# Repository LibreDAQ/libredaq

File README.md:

# LibreDAQ official repository

LibreDAQ is a versatile, modular and hackable Data Acquisition (DAQ) platform. 
This repository includes the sources for: 
* Circuit schematics
* C++ SDK
* C++ examples
* Firmware
* ROS node
* LibreDAQStudio

# Cite as: 

* Blanco-Claraco, J. L., López-Martínez, J., Torres-Moreno, J. L., & Giménez-Fernández, A. (2015). **A Low-Cost Modular Platform for Heterogeneous Data Acquisition with Accurate Interchannel Synchronization**. *Sensors*, 15(10), 27374-27392 ([PDF](https://www.mdpi.com/1424-8220/15/10/27374/pdf)).
* BibTex:
```
@article{blanco2015low,
  title={A Low-Cost Modular Platform for Heterogeneous Data Acquisition with Accurate Interchannel Synchronization},
  author={Blanco-Claraco, Jos{\'e} Luis and L{\'o}pez-Mart{\'\i}nez, Javier and Torres-Moreno, Jos{\'e} Luis and Gim{\'e}nez-Fern{\'a}ndez, Antonio},
  journal={Sensors},
  volume={15},
  number={10},
  pages={27374--27392},
  year={2015}
}
```

# CircuitHub

* [LibreDAQ Base board](https://circuithub.com/projects/LibreDAQ/ldaq-base-v11)

# Videos:

[YouTube playlist](https://www.youtube.com/playlist?list=PLOJ3GF0x2_eULIKMOQqdDnZAjOUo_N2IJ)

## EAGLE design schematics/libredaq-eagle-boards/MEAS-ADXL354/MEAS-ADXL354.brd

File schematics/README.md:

All LibreDAQ schematics are published under the following License:

[Attribution-NonCommercial-ShareAlike 4.0 International](https://creativecommons.org/licenses/by-nc-sa/4.0/)

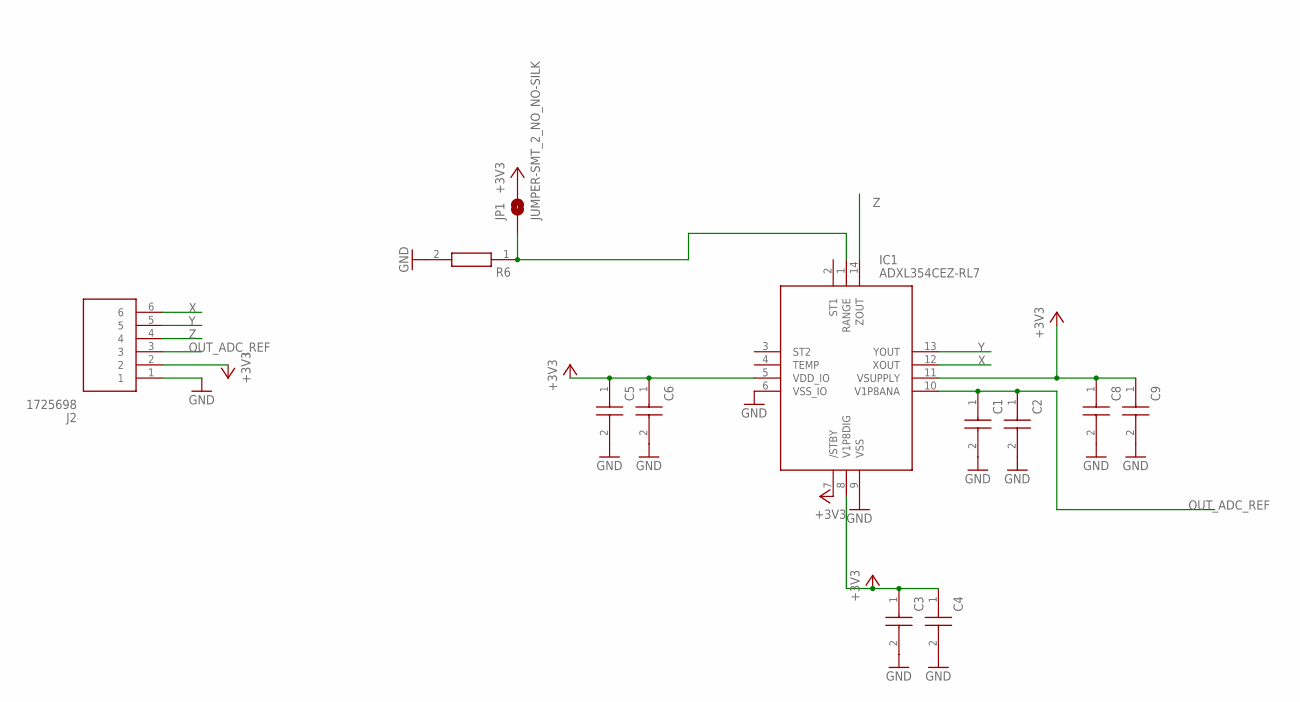
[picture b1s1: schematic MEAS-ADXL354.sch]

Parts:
C1, C3, C5, C8: 1.0uF; CAPC1005X55N
C2, C4, C6, C9: 0.1uF; CAPC1005X55N
IC1: ADXL354CEZ-RL7; PLCC127P602X560X205-14N
J2: 1725698
JP1: JUMPER-SMT_2_NO_NO-SILK; SMT-JUMPER_2_NO_NO-SILK
R6: SFR03EZPF6801; RESC1608X55N

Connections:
+3V3: C3.1, C4.1, C5.1, C6.1, C8.1, C9.1, IC1.5 (VDD_IO), IC1.7 (/STBY), IC1.8 (V1P8DIG), IC1.11 (VSUPPLY), J2.2, JP1.2
GND: C1.2, C2.2, C3.2, C4.2, C5.2, C6.2, C8.2, C9.2, IC1.6 (VSS_IO), IC1.9 (VSS), J2.1, R6.2
unnamed: IC1.1 (RANGE), JP1.1, R6.1
OUT_ADC_REF: C1.1, C2.1, IC1.10 (V1P8ANA), J2.3
X: IC1.12 (XOUT), J2.6
Y: IC1.13 (YOUT), J2.5
Z: IC1.14 (ZOUT), J2.4

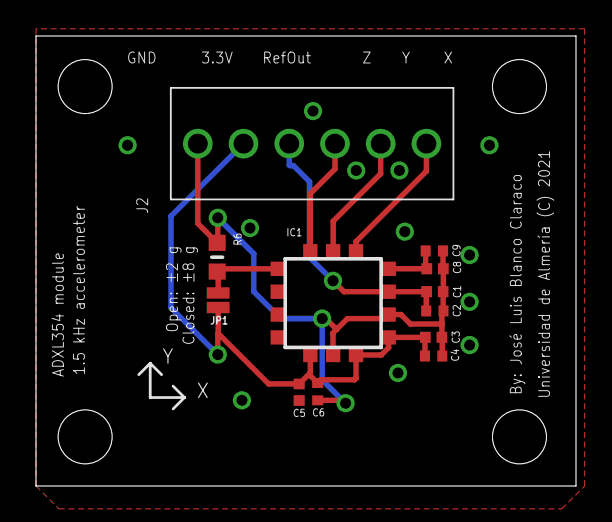
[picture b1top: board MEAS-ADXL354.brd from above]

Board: 2 copper layers, 30.0 x 25.0 mm, 12 parts (0 on the bottom side), 7 nets.

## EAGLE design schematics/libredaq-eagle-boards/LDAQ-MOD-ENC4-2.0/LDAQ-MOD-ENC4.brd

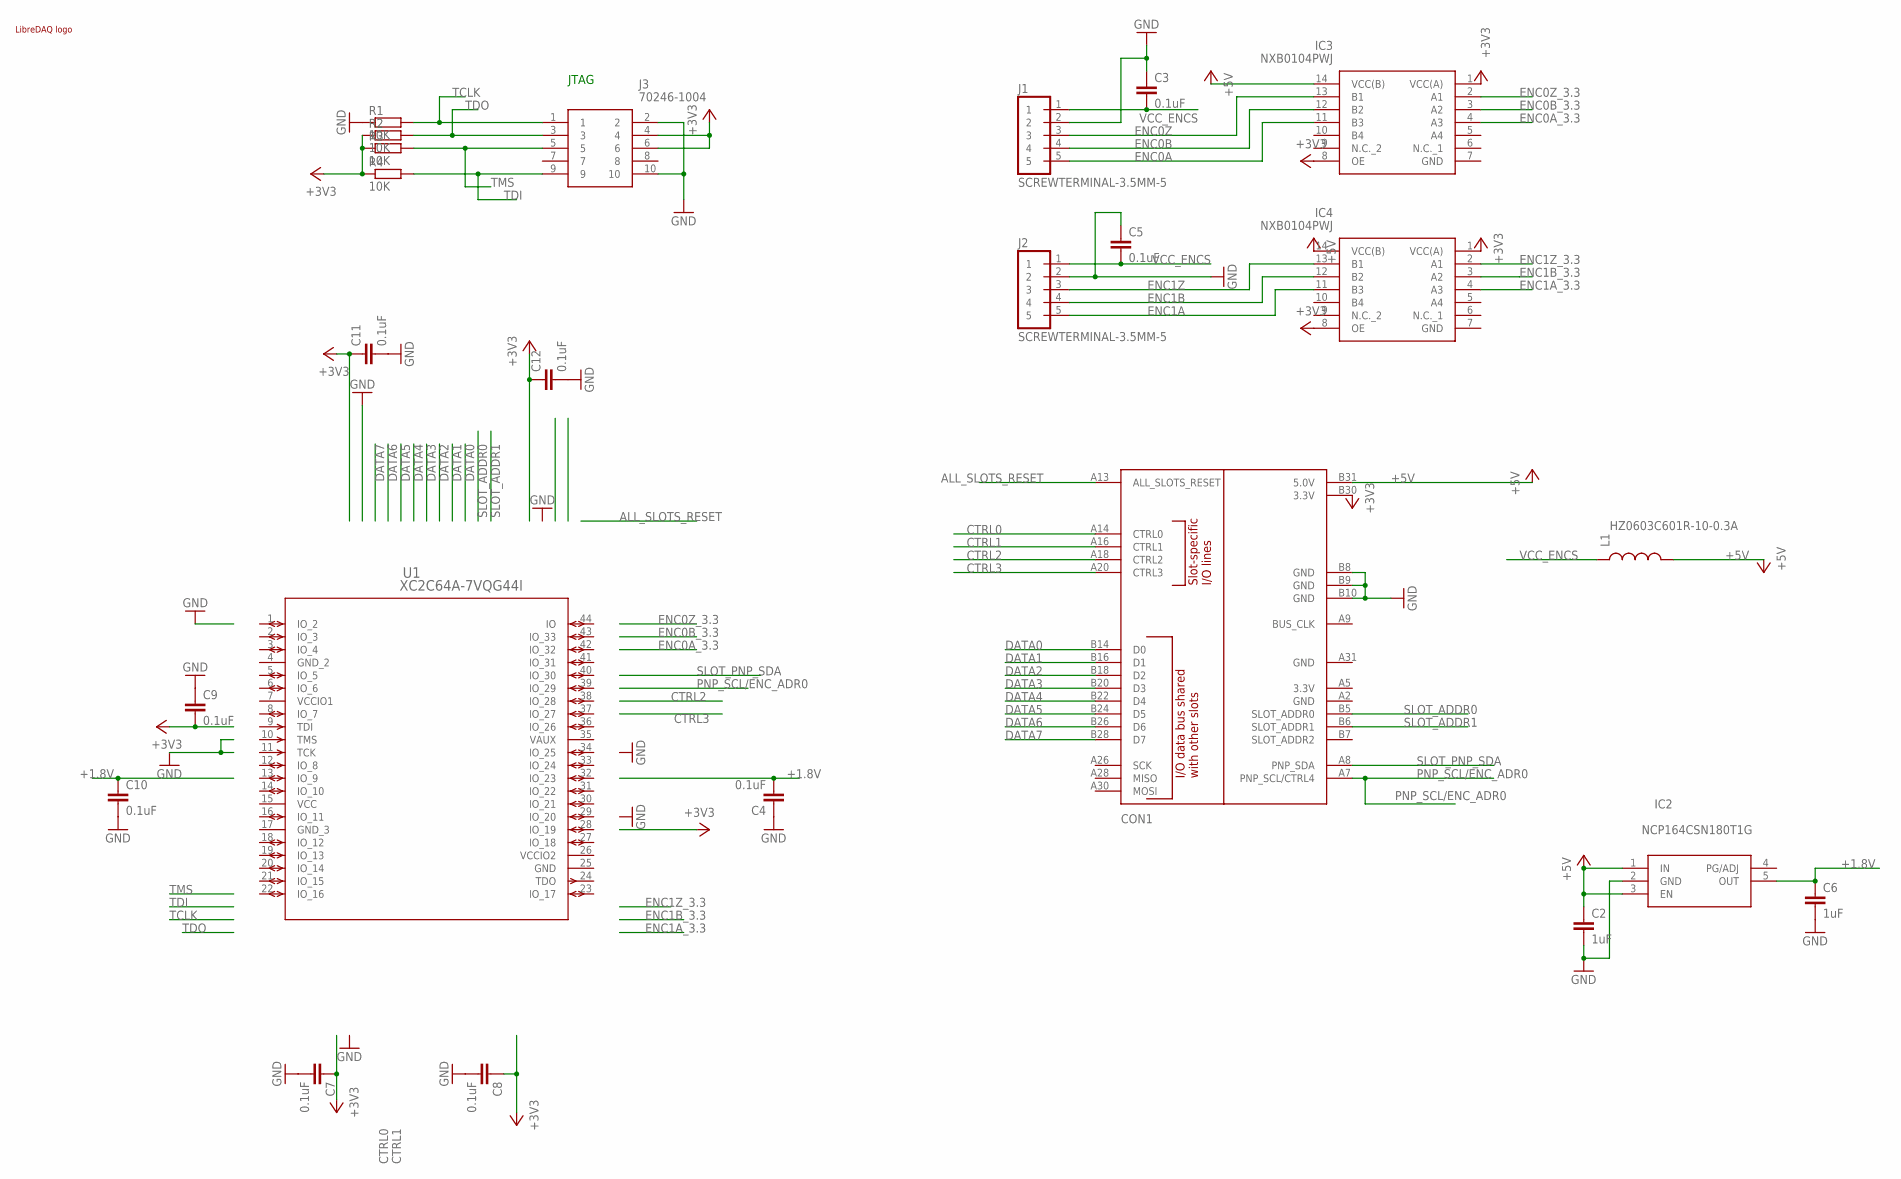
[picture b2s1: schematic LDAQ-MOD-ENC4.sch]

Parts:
C2, C6: 1uF; C0603
C3, C4, C5, C7, C8, C9, C10, C11, C12: 0.1uF; 0603-CAP
CON1: BOARD; PCI-E_64_EDGE_70X60_PADS-ONLY
IC2: NCP164CSN180T1G; SOT95P275X110-5N
IC3, IC4: NXB0104PWJ; SOP65P640X110-14N
J1, J2: SCREWTERMINAL-3.5MM-5
J3: 70246-1004; SHDR10W64P254_2X5_2032X889X927
L1: HZ0603C601R-10-0.3A; 0603
LOGO1: LIBREDAQ_LOGO_MINILOGO_GENERIC; LIBREDAQ_LOGO
R1, R2, R3, R4: 10K; R0603
U1: XC2C64A-7VQG44I; 44-VQFP_XIL

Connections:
+1.8V: C4.2, C6.1, C10.1, IC2.5 (OUT)
+3V3: C7.1, C8.1, C9.2, C11.1, C12.1, CON1.B30 (3.3V), IC3.1 (VCC(A)), IC3.8 (OE), IC4.1 (VCC(A)), IC4.8 (OE), J3.4, J3.6, R2.1, R3.1, R4.1
+5V: C2.1, CON1.B31 (5.0V), IC2.1 (IN), IC2.3 (EN), IC3.14 (VCC(B)), IC4.14 (VCC(B)), L1.2
ALL_SLOTS_RESET: CON1.A13 (ALL_SLOTS_RESET)
CTRL0: CON1.A14 (CTRL0)
CTRL1: CON1.A16 (CTRL1)
CTRL2: CON1.A18 (CTRL2)
CTRL3: CON1.A20 (CTRL3)
DATA0: CON1.B14 (D0)
DATA1: CON1.B16 (D1)
DATA2: CON1.B18 (D2)
DATA3: CON1.B20 (D3)
DATA4: CON1.B22 (D4)
DATA5: CON1.B24 (D5)
DATA6: CON1.B26 (D6)
DATA7: CON1.B28 (D7)
ENC0A: IC3.11 (B3), J1.5
ENC0A_3.3: IC3.4 (A3)
ENC0B: IC3.12 (B2), J1.4
ENC0B_3.3: IC3.3 (A2)
ENC0Z: IC3.13 (B1), J1.3
ENC0Z_3.3: IC3.2 (A1)
ENC1A: IC4.11 (B3), J2.5
ENC1A_3.3: IC4.4 (A3)
ENC1B: IC4.12 (B2), J2.4
ENC1B_3.3: IC4.3 (A2)
ENC1Z: IC4.13 (B1), J2.3
ENC1Z_3.3: IC4.2 (A1)
GND: C2.2, C3.1, C4.1, C5.1, C6.2, C7.2, C8.2, C9.1, C10.2, C11.2, C12.2, CON1.B8 (GND), CON1.B9 (GND), CON1.B10 (GND), IC2.2 (GND), J1.2, J2.2, J3.2, J3.10, R1.1, U1.25 (GND)
GND_2: U1.4 (GND_2)
GND_3: U1.17 (GND_3)
PNP_SCL/ENC_ADR0: CON1.A7 (PNP_SCL/CTRL4)
SLOT_ADDR0: CON1.B5 (SLOT_ADDR0)
SLOT_ADDR1: CON1.B6 (SLOT_ADDR1)
SLOT_PNP_SDA: CON1.A8 (PNP_SDA)
TCLK: J3.1, R1.2
TDI: J3.9, R4.2
TDO: J3.3, R2.2
TMS: J3.5, R3.2
VAUX: U1.35 (VAUX)
VCC: U1.15 (VCC)
VCCIO1: U1.7 (VCCIO1)
VCCIO2: U1.26 (VCCIO2)
VCC_ENCS: C3.2, C5.2, J1.1, J2.1, L1.1

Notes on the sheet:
JTAG

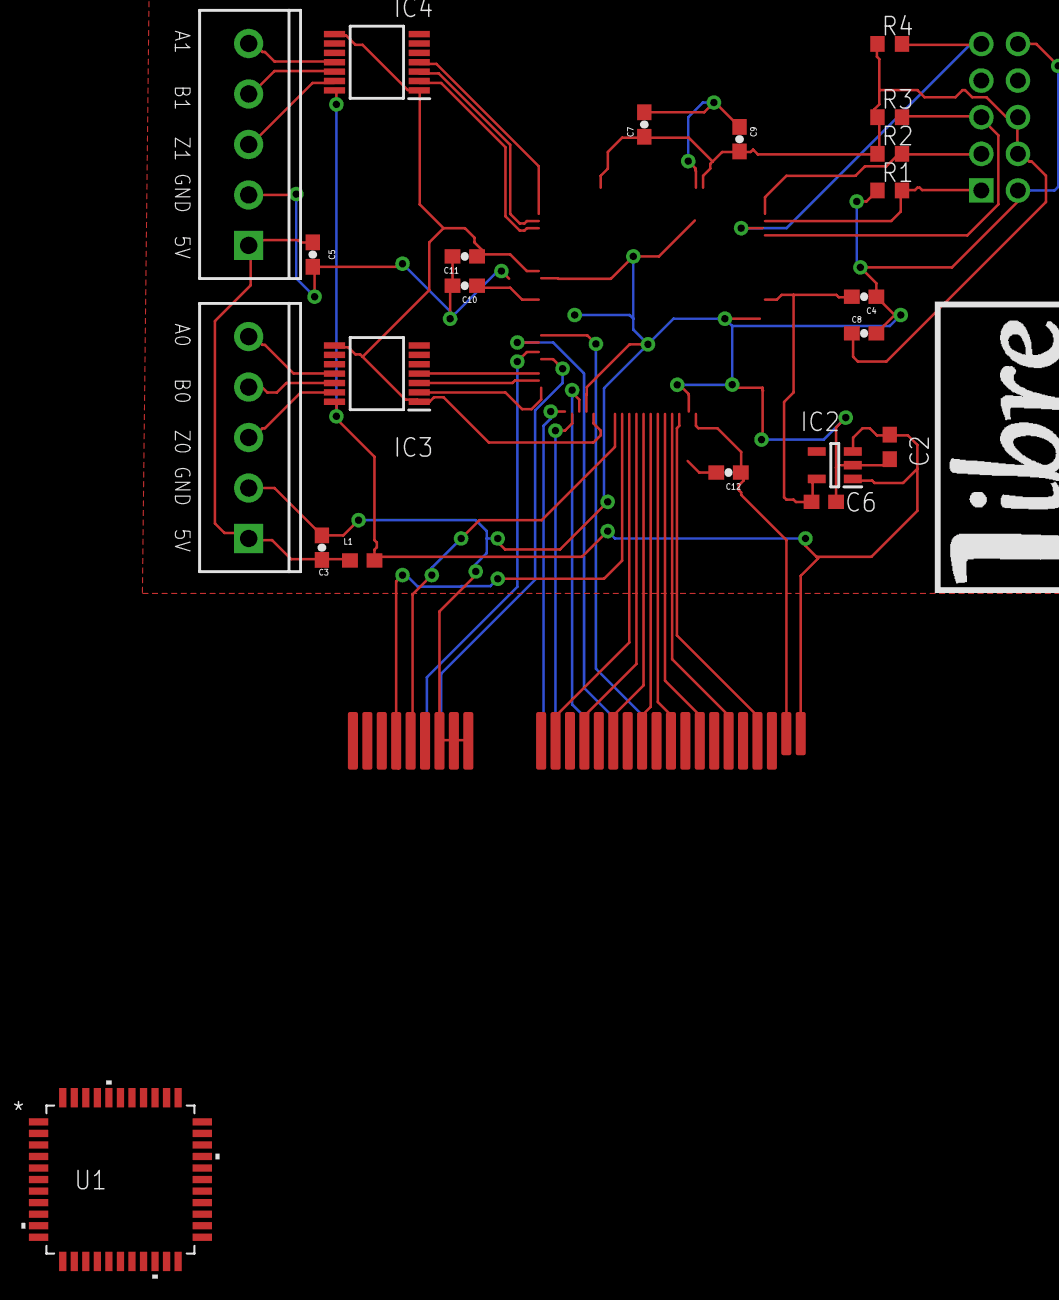
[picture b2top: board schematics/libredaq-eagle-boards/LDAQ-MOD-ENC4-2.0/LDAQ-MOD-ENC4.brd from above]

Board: 2 copper layers, 25 parts (1 on the bottom side), 15 nets.

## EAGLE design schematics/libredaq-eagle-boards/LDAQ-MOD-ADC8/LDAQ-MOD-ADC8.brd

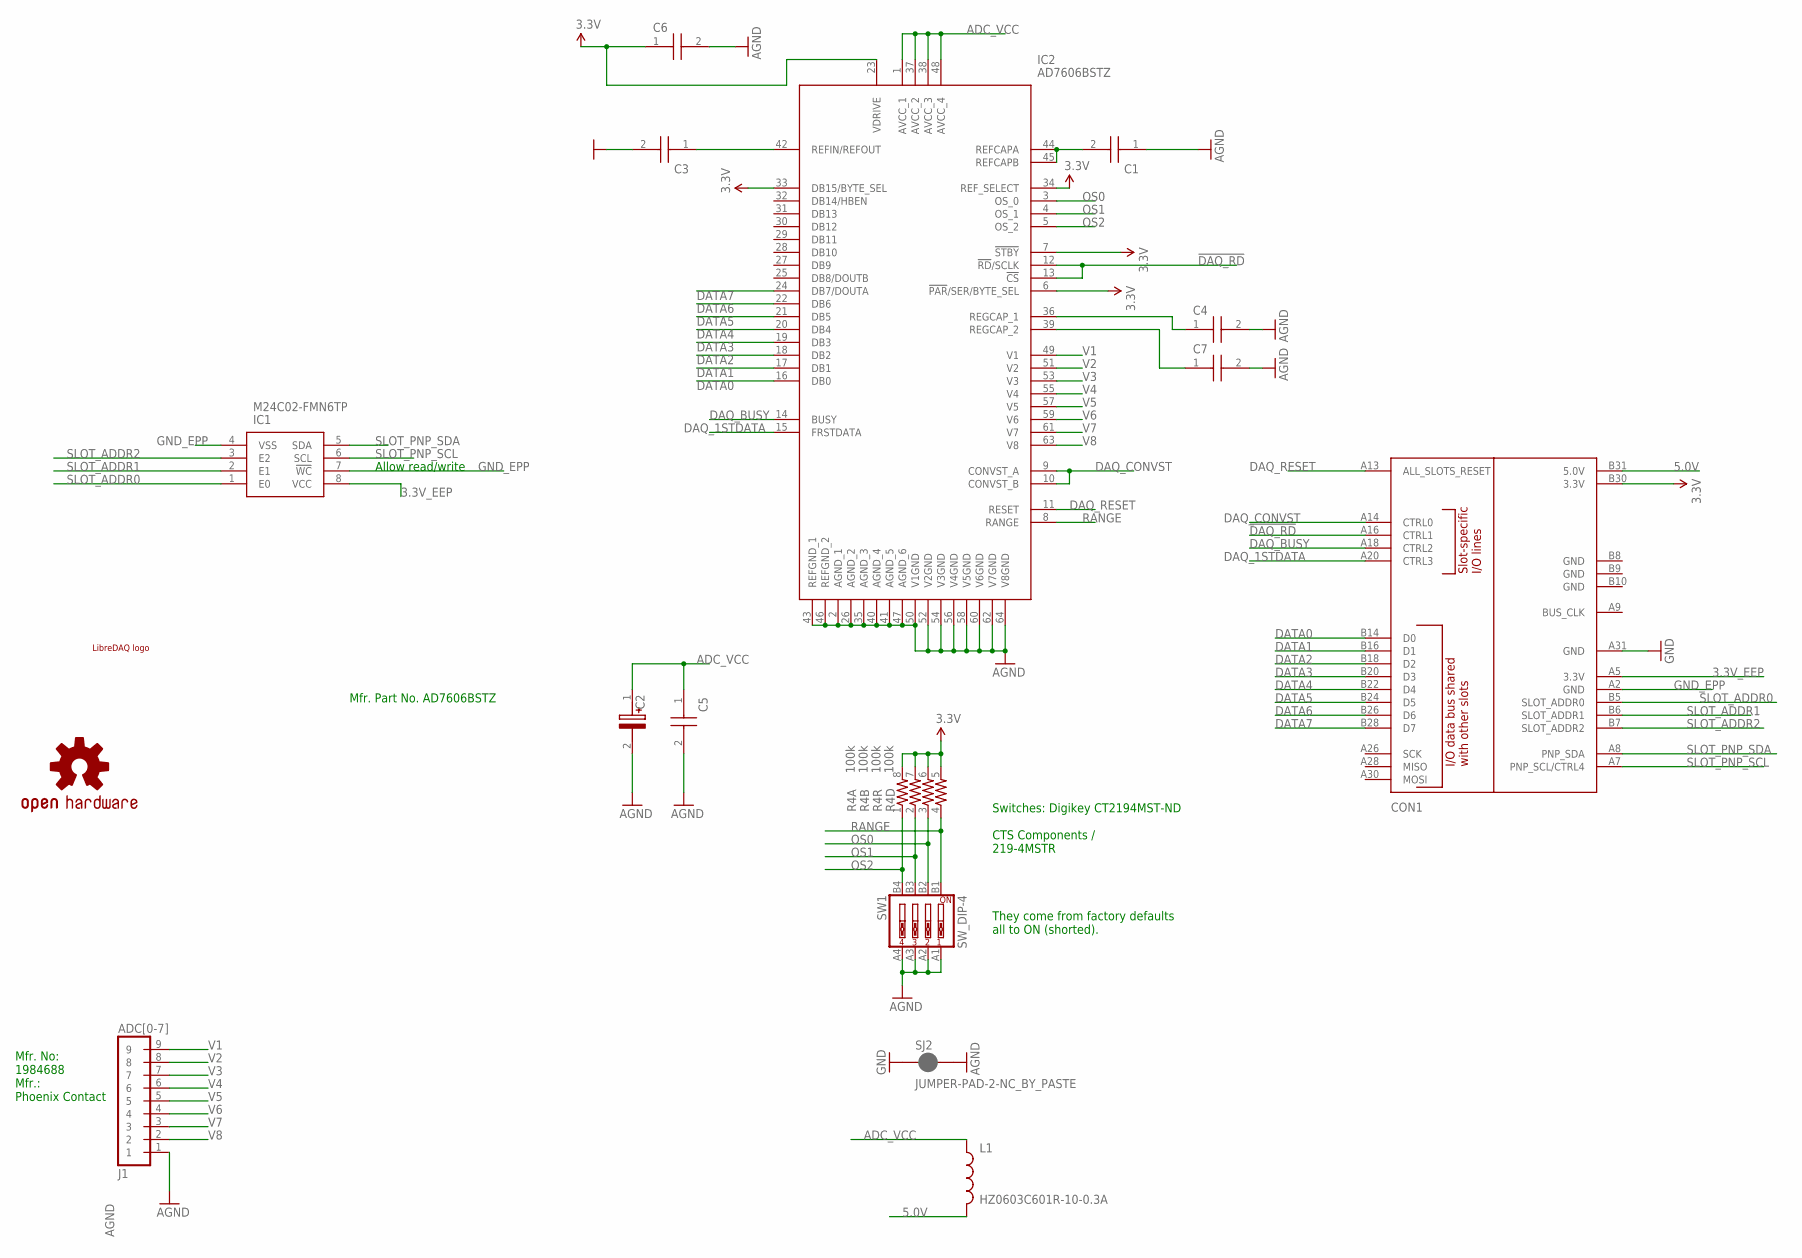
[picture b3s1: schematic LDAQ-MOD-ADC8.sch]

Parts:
C1, C3: 10uF; CAPC1005X55N
C2: 10uF; CAPPM3528X210N
C4, C7: 1.0uF; CAPC1005X55N
C5, C6: 0.1uF; CAPC1005X55N
CON1: BOARD; PCI-E_64_EDGE_63X50
IC1: M24C02-FMN6TP; SOIC127P600X175-8N
IC2: AD7606BSTZ; QFP50P1200X1200X160-64N
J1: ADC[0-7]; SCREWTERMINAL-3.5MM-9
L1: HZ0603C601R-10-0.3A; 0603
LOGO1: LIBREDAQ_LOGO_MINILOGO_GENERIC; LIBREDAQ_LOGO
LOGO2: OSHW-LOGOL; OSHW-LOGO-L
R4: 100k; 0603-ARV
SJ2: JUMPER-PAD-2-NC_BY_PASTE; PAD-JUMPER-2-NC_BY_PASTE_YES_SILK
SW1: SW_DIP-4; SW_SIP-4

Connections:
3.3V: C6.1, CON1.B30 (3.3V), IC2.6 (!PAR!/SER/BYTE_SEL), IC2.7 (!STBY), IC2.23 (VDRIVE), IC2.33 (DB15/BYTE_SEL), IC2.34 (REF_SELECT), R4.5 (2), R4.6 (2), R4.7 (2), R4.8 (2)
3.3V_EEP: CON1.A5 (3.3V), IC1.8 (VCC)
5.0V: CON1.B31 (5.0V), L1.2
!DAQ_RD: CON1.A16 (CTRL1), IC2.12 (!RD!/SCLK), IC2.13 (!CS)
ADC_VCC: C2.1 (+), C5.1, IC2.1 (AVCC_1), IC2.37 (AVCC_2), IC2.38 (AVCC_3), IC2.48 (AVCC_4), L1.1
AGND: C1.1, C2.2 (-), C3.2, C4.2, C5.2, C6.2, C7.2, IC2.2 (AGND_1), IC2.26 (AGND_2), IC2.35 (AGND_3), IC2.40 (AGND_4), IC2.41 (AGND_5), IC2.43 (REFGND_1), IC2.46 (REFGND_2), IC2.47 (AGND_6), IC2.50 (V1GND), IC2.52 (V2GND), IC2.54 (V3GND), IC2.56 (V4GND), IC2.58 (V5GND), IC2.60 (V6GND), IC2.62 (V7GND), IC2.64 (V8GND), J1.1, SJ2.2, SW1.A1, SW1.A2, SW1.A3, SW1.A4
DAQ_1STDATA: CON1.A20 (CTRL3), IC2.15 (FRSTDATA)
DAQ_BUSY: CON1.A18 (CTRL2), IC2.14 (BUSY)
DAQ_CONVST: CON1.A14 (CTRL0), IC2.9 (CONVST_A), IC2.10 (CONVST_B)
DAQ_RESET: CON1.A13 (ALL_SLOTS_RESET), IC2.11 (RESET)
DATA0: CON1.B14 (D0), IC2.16 (DB0)
DATA1: CON1.B16 (D1), IC2.17 (DB1)
DATA2: CON1.B18 (D2), IC2.18 (DB2)
DATA3: CON1.B20 (D3), IC2.19 (DB3)
DATA4: CON1.B22 (D4), IC2.20 (DB4)
DATA5: CON1.B24 (D5), IC2.21 (DB5)
DATA6: CON1.B26 (D6), IC2.22 (DB6)
DATA7: CON1.B28 (D7), IC2.24 (DB7/DOUTA)
GND: CON1.A31 (GND), SJ2.1
GND_EPP: CON1.A2 (GND), IC1.4 (VSS), IC1.7 (!WC)
unnamed: C1.2, IC2.44 (REFCAPA), IC2.45 (REFCAPB)
unnamed: C4.1, IC2.36 (REGCAP_1)
unnamed: C7.1, IC2.39 (REGCAP_2)
unnamed: C3.1, IC2.42 (REFIN/REFOUT)
OS0: IC2.3 (OS_0), R4.3 (1), SW1.B2
OS1: IC2.4 (OS_1), R4.2 (1), SW1.B3
OS2: IC2.5 (OS_2), R4.1, SW1.B4
RANGE: IC2.8 (RANGE), R4.4 (1), SW1.B1
SLOT_ADDR0: CON1.B5 (SLOT_ADDR0), IC1.1 (E0)
SLOT_ADDR1: CON1.B6 (SLOT_ADDR1), IC1.2 (E1)
SLOT_ADDR2: CON1.B7 (SLOT_ADDR2), IC1.3 (E2)
SLOT_PNP_SCL: CON1.A7 (PNP_SCL/CTRL4), IC1.6 (SCL)
SLOT_PNP_SDA: CON1.A8 (PNP_SDA), IC1.5 (SDA)
V1: IC2.49 (V1), J1.9
V2: IC2.51 (V2), J1.8
V3: IC2.53 (V3), J1.7
V4: IC2.55 (V4), J1.6
V5: IC2.57 (V5), J1.5
V6: IC2.59 (V6), J1.4
V7: IC2.61 (V7), J1.3
V8: IC2.63 (V8), J1.2

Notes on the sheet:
Allow read/write
Switches: Digikey CT2194MST-ND CTS Components / 219-4MSTR They come from factory defaults all to ON (shorted).
Mfr. No: 1984688 Mfr.: Phoenix Contact
Mfr. Part No. AD7606BSTZ

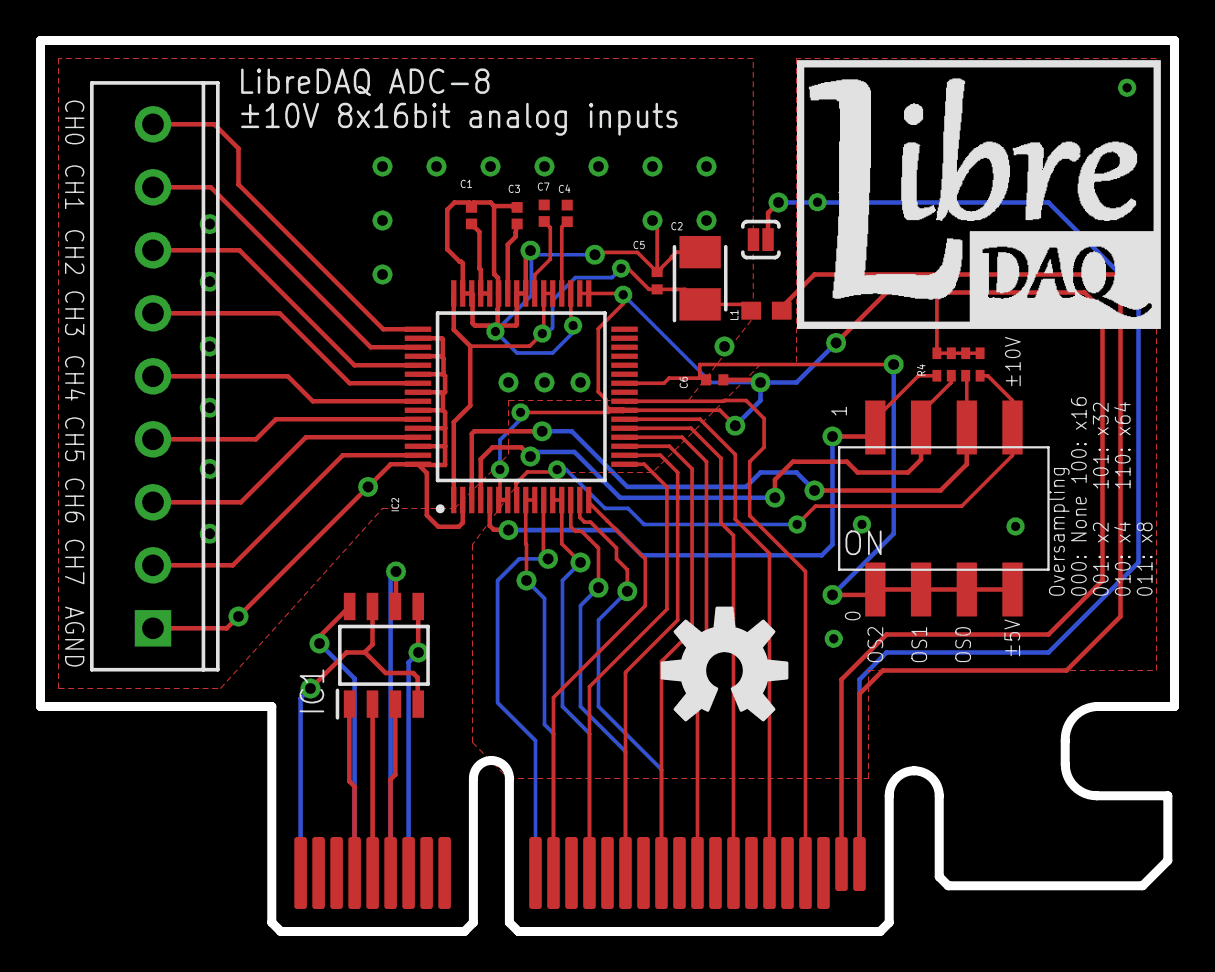
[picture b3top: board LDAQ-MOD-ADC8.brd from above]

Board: 2 copper layers, 63.0 x 49.5 mm, 17 parts (0 on the bottom side), 41 nets.

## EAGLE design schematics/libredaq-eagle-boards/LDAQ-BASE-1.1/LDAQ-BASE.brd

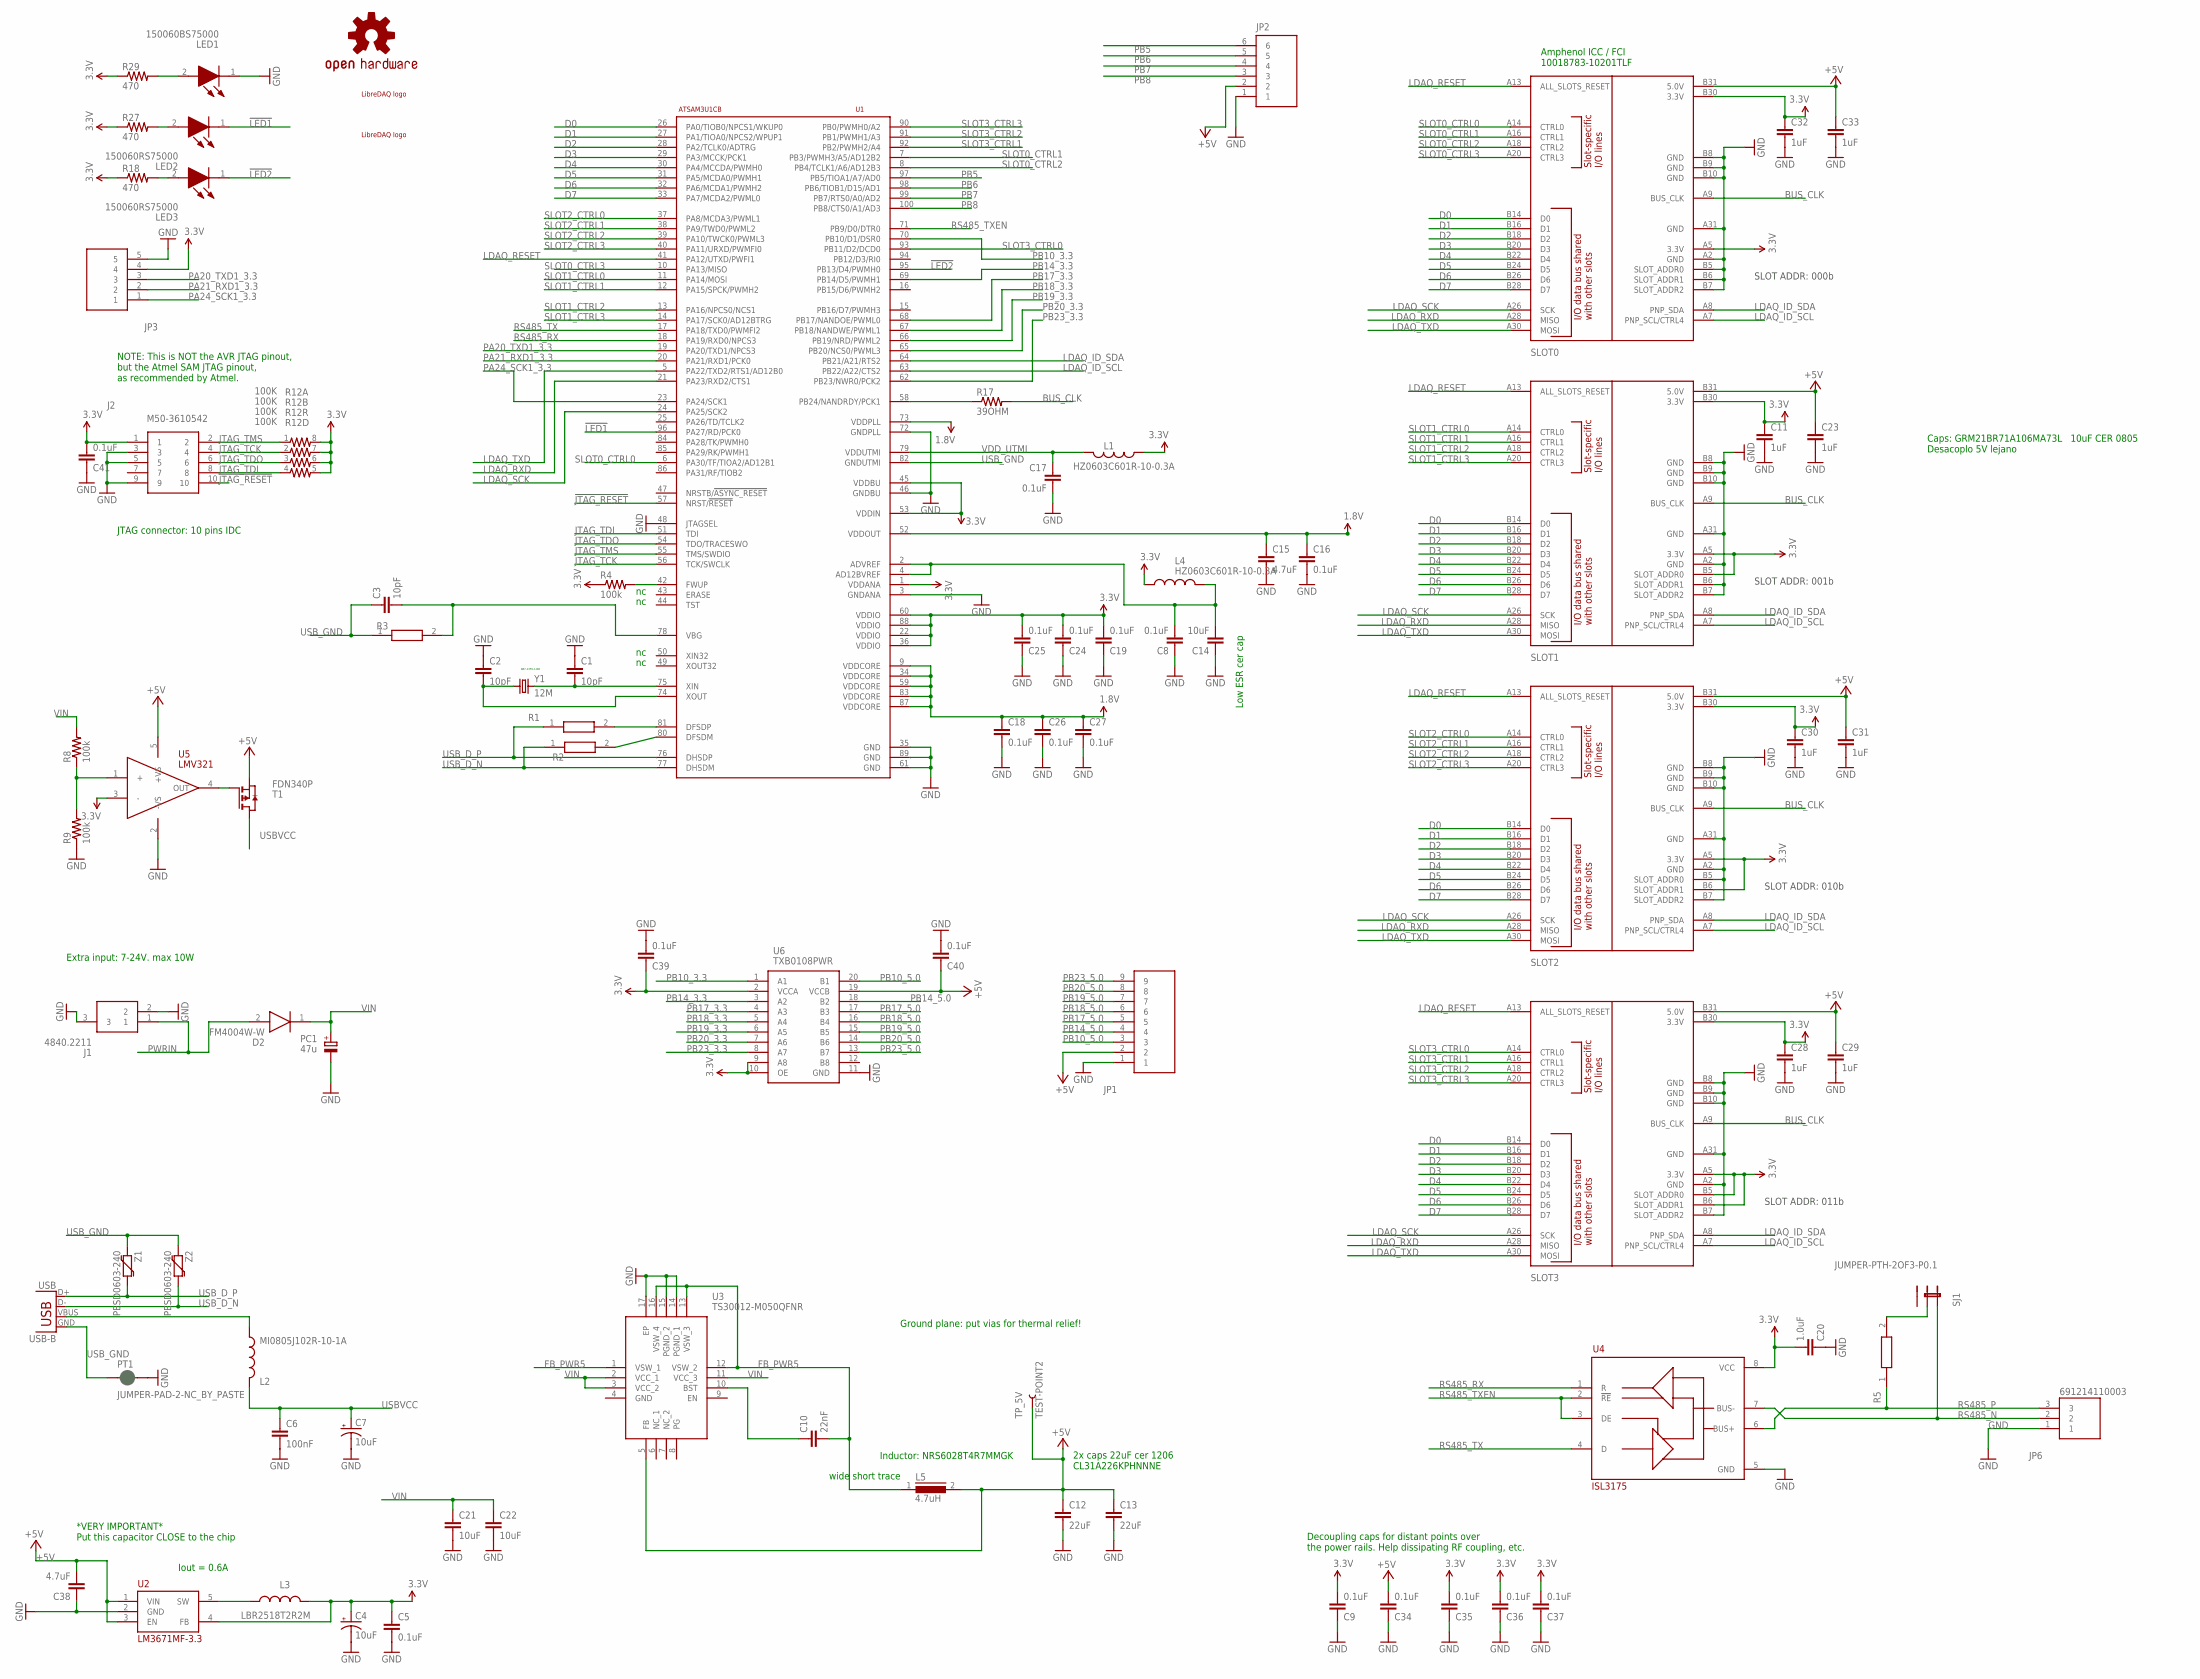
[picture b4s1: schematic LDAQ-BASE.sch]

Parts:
C1, C2, C3: 10pF; 0603-CAP
C4, C7: 10uF; EIA3216
C5, C8, C9, C16, C17, C18, C19, C24, C25, C26, C27, C34, C35, C36, C37, C39, C40, C41: 0.1uF; 0603-CAP
C6: 100nF; 0603-CAP
C10: 22nF; 0603-CAP
C11, C23, C28, C29, C30, C31, C32, C33: 1uF; 0805
C12, C13: 22uF; 1206
C14: 10uF; 0603-CAP
C15, C38: 4.7uF; 0603-CAP
C20: 1.0uF; 0603-CAP
C21, C22: 10uF; 1206
D2: FM4004W-W; DIOM5025X231N
J1: 4840.2211; 48402211
J2: M50-3610542; M503610542
JP1: 39357-0009; 393570009
JP2: 1984659
JP3: 1984646
JP6: 691214110003
L1, L4: HZ0603C601R-10-0.3A; 0603
L2: MI0805J102R-10-1A; 0805
L3: LBR2518T2R2M; 1007
L5: 4.7uH; INDUCTOR_6028
LED1: 150060BS75000; LEDC1608X80N
LED2, LED3: 150060RS75000; LEDC1608X80N
LOGO1: OSHW-LOGOL; OSHW-LOGO-L
PC1: 47u; PANASONIC_D
PT1: JUMPER-PAD-2-NC_BY_PASTE; PAD-JUMPER-2-NC_BY_PASTE_YES_SILK
R1, R2: CR1206-FX-39R0ELF; RESC3216X75N
R3: SFR03EZPF6801; RESC1608X55N
R4, R8, R9: 100k; 0603-RES
R5: CRCW0603120RFKEAC; RESC1608X55N
R12: 100K; 0603-ARV
R17: 39OHM; 0603@1
R18, R27, R29: 470; 0603-RES
SJ1: JUMPER-PTH-2OF3-P0.1; 1X03_LONGPADS
SLOT0, SLOT1, SLOT2, SLOT3: SLOT; PCI-E_64_PTH_CONN
T1: FDN340P; SOT-23
TP_5V: TEST-POINT2; PAD.02X.02
U1: ATSAM3U1CB; TQFP100
U2: LM3671MF-3.3; TOP23-5
U3: TS30012-M050QFNR; QFN50P300X300X100-17N
U4: ISL3175; SOIC8
U5: LMV321; SOT353-SC70-5
U6: TXB0108PWR; SOP65P640X120-20N
U$1: LIBREDAQ_LOGO_MINILOGO_GENERIC; LIBREDAQ_LOGO
U$6: LOGO_INDALO; LIBREDAQ_LOGO_INDALO_ALMERIA
USB: USB-B; USB-B-PTH
Y1: 12M; CRYSTAL-SMD-5X3
Z1, Z2: PESD0603-240; 0603-RES

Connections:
1.8V: C15.1, C16.1, C18.1, C26.1, C27.1, U1.9 (VDDCORE), U1.34 (VDDCORE), U1.52 (VDDOUT), U1.59 (VDDCORE), U1.73 (VDDPLL), U1.83 (VDDCORE), U1.87 (VDDCORE)
3.3V: C4.A (+), C5.1, C9.2, C11.1, C19.2, C20.2, C24.2, C25.2, C28.1, C30.1, C32.1, C35.2, C36.2, C37.2, C39.1, C41.2, J2.1, JP3.4, L1.2, L3.2, L4.1, R4.1, R12.5 (2), R12.6 (2), R12.7 (2), R12.8 (2), R18.1, R27.1, R29.1, SLOT0.A5 (3.3V), SLOT0.B30 (3.3V), SLOT1.A5 (3.3V), SLOT1.B5 (SLOT_ADDR0), SLOT1.B30 (3.3V), SLOT2.A5 (3.3V), SLOT2.B6 (SLOT_ADDR1), SLOT2.B30 (3.3V), SLOT3.A5 (3.3V), SLOT3.B5 (SLOT_ADDR0), SLOT3.B6 (SLOT_ADDR1), SLOT3.B30 (3.3V), U1.1 (VDDANA), U1.22 (VDDIO), U1.36 (VDDIO), U1.45 (VDDBU), U1.53 (VDDIN), U1.60 (VDDIO), U1.88 (VDDIO), U2.4 (FB), U4.8 (VCC), U5.3 (-), U6.2 (VCCA), U6.9 (A8), U6.10 (OE)
!JTAG_RESET: J2.10, U1.57 (NRST/!RESET)
!LED1: LED2.1 (K), U1.96 (PA27/RD/PCK0)
!LED2: LED3.1 (K), U1.95 (PB13/D4/PWMH0)
+5V: C12.1, C13.1, C23.1, C29.1, C31.1, C33.1, C34.2, C38.2, C40.1, JP1.2, JP2.2, L5.2, SLOT0.B31 (5.0V), SLOT1.B31 (5.0V), SLOT2.B31 (5.0V), SLOT3.B31 (5.0V), T1.2 (S), TP_5V.P$1, U2.1 (VIN), U2.3 (EN), U3.5 (FB), U5.5 (+VS), U6.19 (VCCB)
BUS_CLK: R17.2, SLOT0.A9 (BUS_CLK), SLOT1.A9 (BUS_CLK), SLOT2.A9 (BUS_CLK), SLOT3.A9 (BUS_CLK)
CMP: R8.1, R9.2, U5.1 (+)
D0: SLOT0.B14 (D0), SLOT1.B14 (D0), SLOT2.B14 (D0), SLOT3.B14 (D0), U1.26 (PA0/TIOB0/NPCS1/WKUP0)
D1: SLOT0.B16 (D1), SLOT1.B16 (D1), SLOT2.B16 (D1), SLOT3.B16 (D1), U1.27 (PA1/TIOA0/NPCS2/WPUP1)
D2: SLOT0.B18 (D2), SLOT1.B18 (D2), SLOT2.B18 (D2), SLOT3.B18 (D2), U1.28 (PA2/TCLK0/ADTRG)
D3: SLOT0.B20 (D3), SLOT1.B20 (D3), SLOT2.B20 (D3), SLOT3.B20 (D3), U1.29 (PA3/MCCK/PCK1)
D4: SLOT0.B22 (D4), SLOT1.B22 (D4), SLOT2.B22 (D4), SLOT3.B22 (D4), U1.30 (PA4/MCCDA/PWMH0)
D5: SLOT0.B24 (D5), SLOT1.B24 (D5), SLOT2.B24 (D5), SLOT3.B24 (D5), U1.31 (PA5/MCDA0/PWMH1)
D6: SLOT0.B26 (D6), SLOT1.B26 (D6), SLOT2.B26 (D6), SLOT3.B26 (D6), U1.32 (PA6/MCDA1/PWMH2)
D7: SLOT0.B28 (D7), SLOT1.B28 (D7), SLOT2.B28 (D7), SLOT3.B28 (D7), U1.33 (PA7/MCDA2/PWML0)
FB_PWR5: C10.2, L5.1, U3.1 (VSW_1), U3.12 (VSW_2), U3.13 (VSW_3), U3.16 (VSW_4)
GND: C1.1, C2.1, C4.C (-), C5.2, C6.2, C7.C (-), C8.1, C9.1, C11.2, C12.2, C13.2, C14.1, C15.2, C16.2, C17.2, C18.2, C19.1, C20.1, C21.2, C22.2, C23.2, C24.1, C25.1, C26.2, C27.2, C28.2, C29.2, C30.2, C31.2, C32.2, C33.2, C34.1, C35.1, C36.1, C37.1, C38.1, C39.2, C40.2, C41.1, J1.2, J1.3, J2.3, J2.5, J2.9, JP1.1, JP2.1, JP3.5, JP6.1, LED1.1 (K), PC1.-, PT1.2, R9.1, SLOT0.A2 (GND), SLOT0.A31 (GND), SLOT0.B5 (SLOT_ADDR0), SLOT0.B6 (SLOT_ADDR1), SLOT0.B7 (SLOT_ADDR2), SLOT0.B8 (GND), SLOT0.B9 (GND), SLOT0.B10 (GND), SLOT1.A2 (GND), SLOT1.A31 (GND), SLOT1.B6 (SLOT_ADDR1), SLOT1.B7 (SLOT_ADDR2), SLOT1.B8 (GND), SLOT1.B9 (GND), SLOT1.B10 (GND), SLOT2.A2 (GND), SLOT2.A31 (GND), SLOT2.B5 (SLOT_ADDR0), SLOT2.B7 (SLOT_ADDR2), SLOT2.B8 (GND), SLOT2.B9 (GND), SLOT2.B10 (GND), SLOT3.A2 (GND), SLOT3.A31 (GND), SLOT3.B7 (SLOT_ADDR2), SLOT3.B8 (GND), SLOT3.B9 (GND), SLOT3.B10 (GND), U1.3 (GNDANA), U1.35 (GND), U1.46 (GNDBU), U1.48 (JTAGSEL), U1.61 (GND), U1.72 (GNDPLL), U1.89 (GND), U2.2 (GND), U3.14 (PGND_1), U3.15 (PGND_2), U3.17 (EP), U4.5 (GND), U5.2 (-VS), U6.11 (GND)
JTAG_TCK: J2.4, R12.2 (1), U1.56 (TCK/SWCLK)
JTAG_TDI: J2.8, R12.4 (1), U1.51 (TDI)
JTAG_TDO: J2.6, R12.3 (1), U1.54 (TDO/TRACESWO)
JTAG_TMS: J2.2, R12.1, U1.55 (TMS/SWDIO)
LDAQ_ID_SCL: SLOT0.A7 (PNP_SCL/CTRL4), SLOT1.A7 (PNP_SCL/CTRL4), SLOT2.A7 (PNP_SCL/CTRL4), SLOT3.A7 (PNP_SCL/CTRL4), U1.63 (PB22/A22/CTS2)
LDAQ_ID_SDA: SLOT0.A8 (PNP_SDA), SLOT1.A8 (PNP_SDA), SLOT2.A8 (PNP_SDA), SLOT3.A8 (PNP_SDA), U1.64 (PB21/A21/RTS2)
LDAQ_RESET: SLOT0.A13 (ALL_SLOTS_RESET), SLOT1.A13 (ALL_SLOTS_RESET), SLOT2.A13 (ALL_SLOTS_RESET), SLOT3.A13 (ALL_SLOTS_RESET), U1.41 (PA12/UTXD/PWFI1)
LDAQ_RXD: SLOT0.A28 (MISO), SLOT1.A28 (MISO), SLOT2.A28 (MISO), SLOT3.A28 (MISO), U1.21 (PA23/RXD2/CTS1)
LDAQ_SCK: SLOT0.A26 (SCK), SLOT1.A26 (SCK), SLOT2.A26 (SCK), SLOT3.A26 (SCK), U1.24 (PA25/SCK2)
LDAQ_TXD: SLOT0.A30 (MOSI), SLOT1.A30 (MOSI), SLOT2.A30 (MOSI), SLOT3.A30 (MOSI), U1.5 (PA22/TXD2/RTS1/AD12B0)
unnamed: C1.2, U1.75 (XIN), Y1.3 (2)
unnamed: C2.2, U1.74 (XOUT), Y1.1
unnamed: R1.2, U1.81 (DFSDP)
unnamed: R2.2, U1.80 (DFSDM)
unnamed: C3.2, R3.2, U1.78 (VBG)
unnamed: R4.2, U1.42 (FWUP)
unnamed: L2.2, USB.VBUS
unnamed: L3.1, U2.5 (SW)
unnamed: R5.2, SJ1.2
unnamed: LED1.2 (A), R29.2
unnamed: C10.1, U3.10 (BST)
unnamed: T1.3 (G), U5.4 (OUT)
unnamed: R17.1, U1.58 (PB24/NANDRDY/PCK1)
unnamed: C8.2, C14.2, L4.2, U1.2 (ADVREF), U1.4 (AD12BVREF)
unnamed: LED2.2 (A), R27.2
unnamed: LED3.2 (A), R18.2
PA20_TXD1_3.3: JP3.3, U1.19 (PA20/TXD1/NPCS3)
PA21_RXD1_3.3: JP3.2, U1.20 (PA21/RXD1/PCK0)
PA24_SCK1_3.3: JP3.1, U1.23 (PA24/SCK1)
PB5: JP2.6, U1.97 (PB5/TIOA1/A7/AD0)
PB6: JP2.5, U1.98 (PB6/TIOB1/D15/AD1)
PB7: JP2.4, U1.99 (PB7/RTS0/A0/AD2)
PB8: JP2.3, U1.100 (PB8/CTS0/A1/AD3)
PB10_3.3: U1.70 (PB10/D1/DSR0), U6.1 (A1)
PB10_5.0: JP1.3, U6.20 (B1)
PB14_3.3: U1.69 (PB14/D5/PWMH1), U6.3 (A2)
PB14_5.0: JP1.4, U6.18 (B2)
PB17_3.3: U1.68 (PB17/NANDOE/PWML0), U6.4 (A3)
PB17_5.0: JP1.5, U6.17 (B3)
PB18_3.3: U1.67 (PB18/NANDWE/PWML1), U6.5 (A4)
PB18_5.0: JP1.6, U6.16 (B4)
PB19_3.3: U1.66 (PB19/NRD/PWML2), U6.6 (A5)
PB19_5.0: JP1.7, U6.15 (B5)
PB20_3.3: U1.65 (PB20/NCS0/PWML3), U6.7 (A6)
PB20_5.0: JP1.8, U6.14 (B6)
PB23_3.3: U1.62 (PB23/NWR0/PCK2), U6.8 (A7)
PB23_5.0: JP1.9, U6.13 (B7)
PWRIN: D2.2 (A), J1.1
RS485_N: JP6.2, SJ1.1, U4.7 (BUS-)
RS485_P: JP6.3, R5.1, U4.6 (BUS+)
RS485_RX: U1.18 (PA19/RXD0/NPCS3), U4.1 (R)
RS485_TX: U1.17 (PA18/TXD0/PWMFI2), U4.4 (D)
RS485_TXEN: U1.71 (PB9/D0/DTR0), U4.2 (!RE), U4.3 (DE)
SLOT0_CTRL0: SLOT0.A14 (CTRL0), U1.6 (PA30/TF/TIOA2/AD12B1)
SLOT0_CTRL1: SLOT0.A16 (CTRL1), U1.7 (PB3/PWMH3/A5/AD12B2)
SLOT0_CTRL2: SLOT0.A18 (CTRL2), U1.8 (PB4/TCLK1/A6/AD12B3)
SLOT0_CTRL3: SLOT0.A20 (CTRL3), U1.10 (PA13/MISO)
SLOT1_CTRL0: SLOT1.A14 (CTRL0), U1.11 (PA14/MOSI)
SLOT1_CTRL1: SLOT1.A16 (CTRL1), U1.12 (PA15/SPCK/PWMH2)
SLOT1_CTRL2: SLOT1.A18 (CTRL2), U1.13 (PA16/NPCS0/NCS1)
SLOT1_CTRL3: SLOT1.A20 (CTRL3), U1.14 (PA17/SCK0/AD12BTRG)
SLOT2_CTRL0: SLOT2.A14 (CTRL0), U1.37 (PA8/MCDA3/PWML1)
SLOT2_CTRL1: SLOT2.A16 (CTRL1), U1.38 (PA9/TWD0/PWML2)
SLOT2_CTRL2: SLOT2.A18 (CTRL2), U1.39 (PA10/TWCK0/PWML3)
SLOT2_CTRL3: SLOT2.A20 (CTRL3), U1.40 (PA11/URXD/PWMFI0)
SLOT3_CTRL0: SLOT3.A14 (CTRL0), U1.93 (PB11/D2/DCD0)
SLOT3_CTRL1: SLOT3.A16 (CTRL1), U1.92 (PB2/PWMH2/A4)
SLOT3_CTRL2: SLOT3.A18 (CTRL2), U1.91 (PB1/PWMH1/A3)
SLOT3_CTRL3: SLOT3.A20 (CTRL3), U1.90 (PB0/PWMH0/A2)
USBVCC: C6.1, C7.A (+), L2.1, T1.1 (D)
USB_D_N: R2.1, U1.77 (DHSDM), USB.D-, Z2.2
USB_D_P: R1.1, U1.76 (DHSDP), USB.D+, Z1.2
USB_GND: C3.1, PT1.1, R3.1, U1.82 (GNDUTMI), USB.GND, Z1.1, Z2.1
VDD_UTMI: C17.1, L1.1, U1.79 (VDDUTMI)
VIN: C21.1, C22.1, D2.1 (K), PC1.+, R8.2, U3.2 (VCC_1), U3.3 (VCC_2), U3.11 (VCC_3)

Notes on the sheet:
887-2355-1-ND
Low ESR cer cap
Caps: GRM21BR71A106MA73L 10uF CER 0805 Desacoplo 5V lejano
2x caps 22uF cer 1206 CL31A226KPHNNNE
Ground plane: put vias for thermal relief!
Inductor: NRS6028T4R7MMGK
Iout = 0.6A
Extra input: 7-24V. max 10W
wide short trace
SLOT ADDR: 000b
SLOT ADDR: 001b
SLOT ADDR: 010b
SLOT ADDR: 011b
Decoupling caps for distant points over the power rails. Help dissipating RF coupling, etc.
NOTE: This is NOT the AVR JTAG pinout, but the Atmel SAM JTAG pinout, as recommended by Atmel.
*VERY IMPORTANT* Put this capacitor CLOSE to the chip
JTAG connector: 10 pins IDC
Amphenol ICC / FCI 10018783-10201TLF

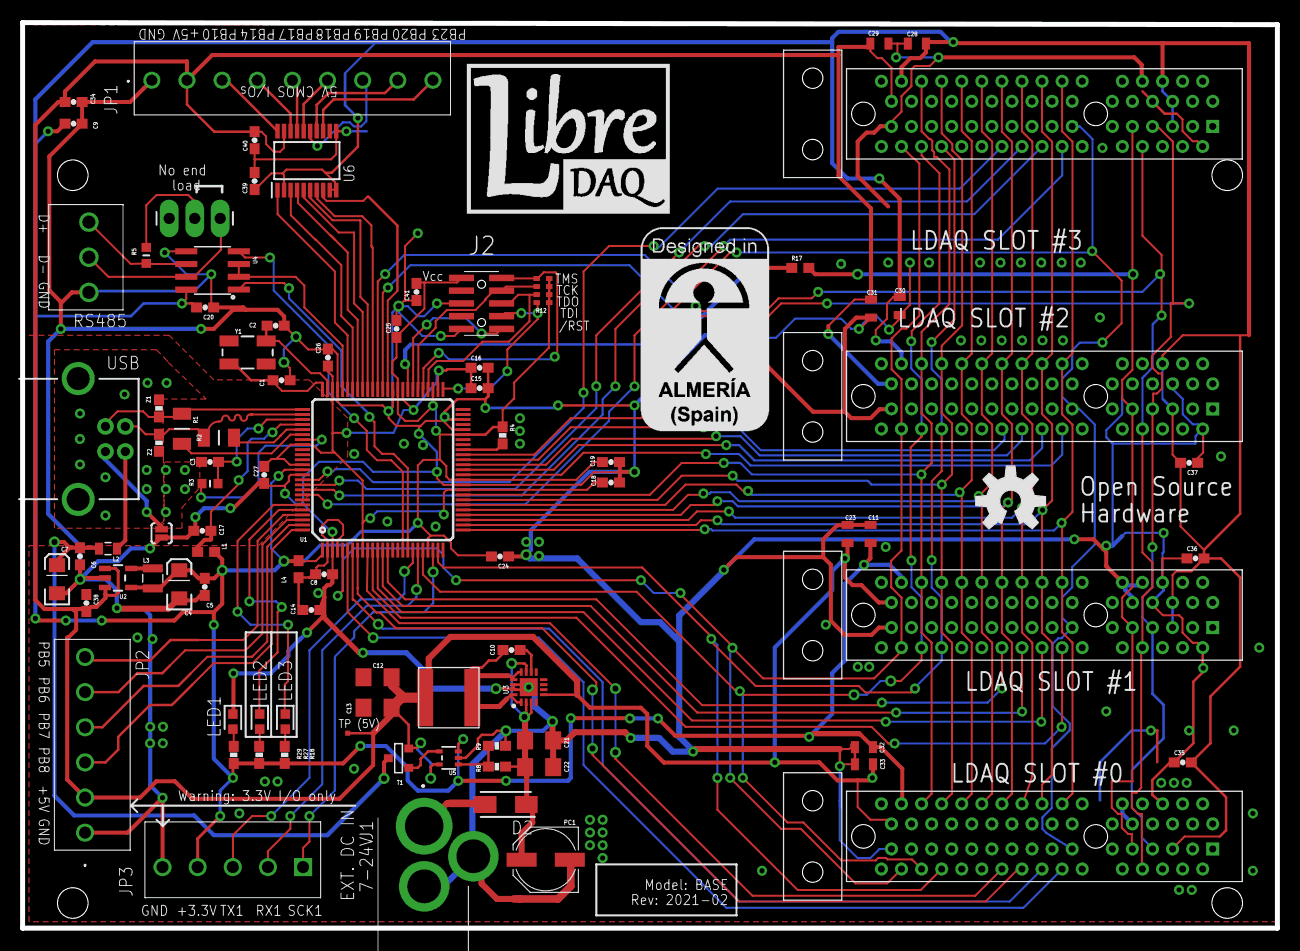
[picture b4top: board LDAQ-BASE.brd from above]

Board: 2 copper layers, 125.0 x 90.2 mm, 94 parts (0 on the bottom side), 93 nets.

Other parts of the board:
U$2, U$3, U$4, U$5: STAND-OFF-TIGHT

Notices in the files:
schematics/libredaq-eagle-boards/MEAS-832M1/MEAS-832M1.brd:
Universidad de Almería (C) 2020
schematics/libredaq-eagle-boards/MEAS-ADXL354/MEAS-ADXL354.brd:
Universidad de Almería (C) 2021
parts and their libraries:
SparkFun-Connectors: Licensing: Creative Commons ShareAlike 4.0 International - https://creativecommons.org/licenses/by-sa/4.0
libredaq-comps: Jose-Luis Blanco (C) 2015
COPYRIGHT: Copyright (C) 2021 Ultra Librarian. All rights reserved.
